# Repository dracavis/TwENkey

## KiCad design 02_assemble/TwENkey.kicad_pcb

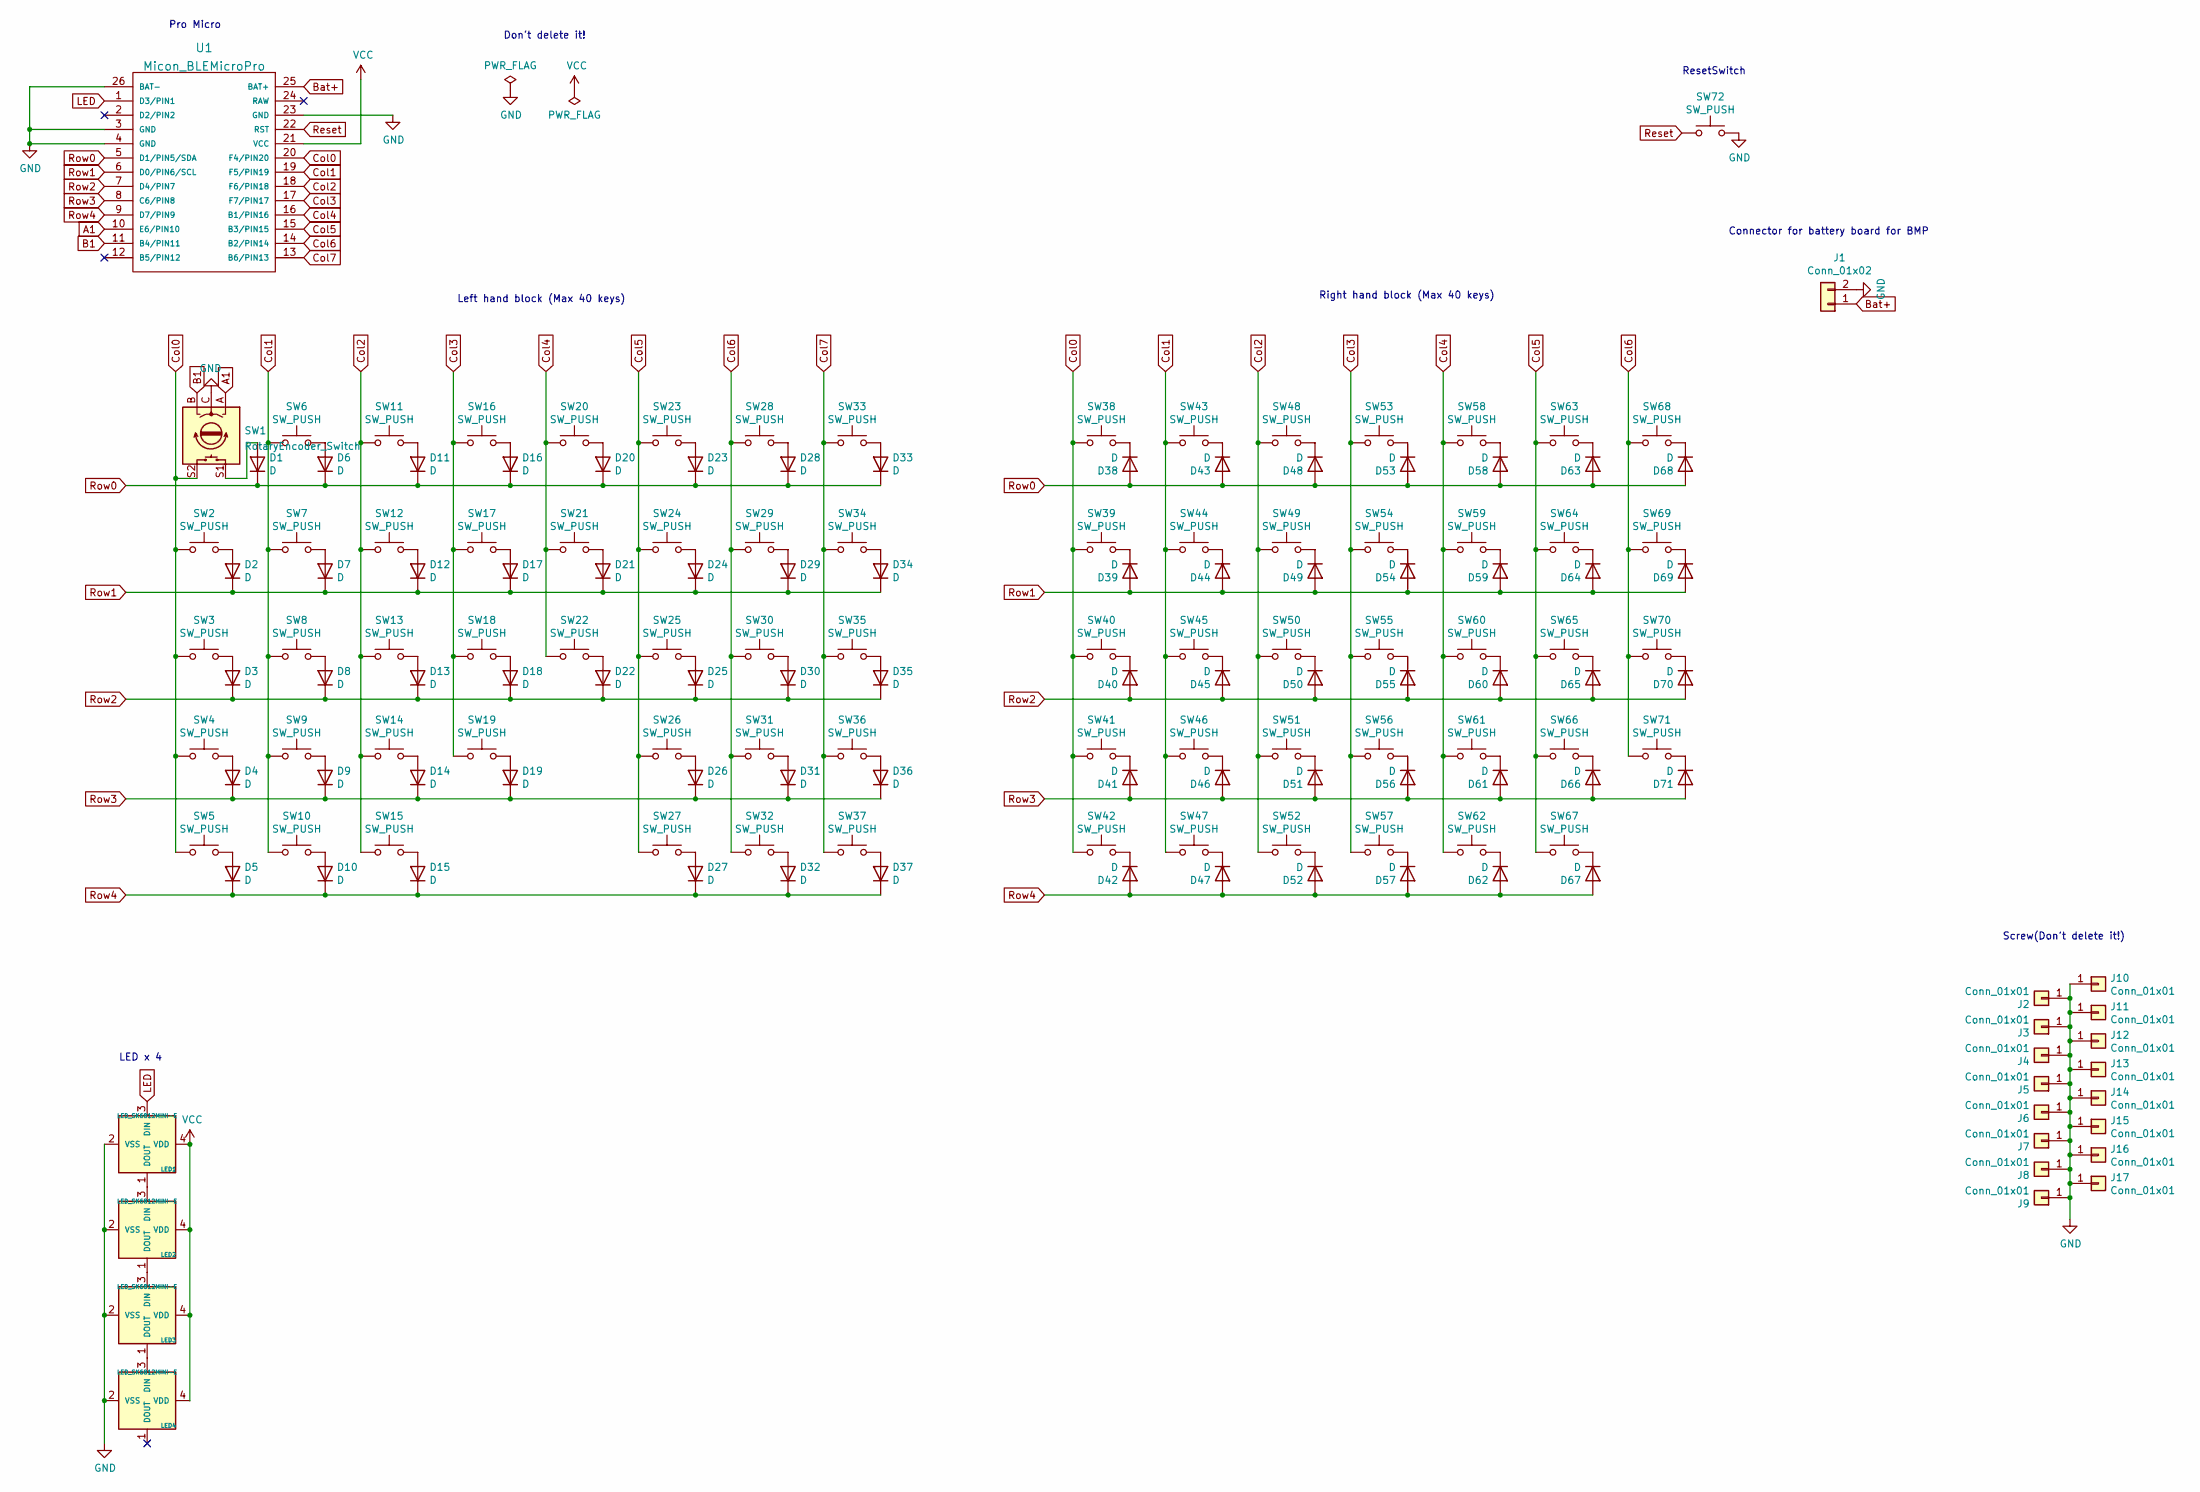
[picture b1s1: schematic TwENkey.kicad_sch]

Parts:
D1, D2, D3, D4, D5, D6, D7, D8, D9, D10, D11, D12, D13, D14, D15, D16, D17, D18, D19, D20, D21, D22, D23, D24, D25, D26, D27, D28, D29, D30, D31, D32, D33, D34, D35, D36, D37, D38, D39, D40, D41, D42, D43, D44, D45, D46, D47, D48, D49, D50, D51, D52, D53, D54, D55, D56, D57, D58, D59, D60, D61, D62, D63, D64, D65, D66, D67, D68, D69, D70, D71: D; Diode_TH_SMD
J1: Conn_01x02; Battery_XH2.5_GL_PCB
J2, J6, J7, J8, J9, J11, J13, J15, J16, J17: Conn_01x01; m2_Screw_Hole_Fab
J3, J4, J5, J10, J12, J14: Conn_01x01; m2_Screw_Hole_EdgeCuts
LED1, LED2, LED3, LED4: LED_SK6812MINI-E; LED_SK6812MINI-E_BL
SW1: RotaryEncoder_Switch; RotaryEncoder_EC12E
SW2, SW3, SW4, SW5, SW6, SW7, SW8, SW9, SW10, SW11, SW12, SW13, SW14, SW15, SW16, SW17, SW18, SW20, SW21, SW22, SW23, SW24, SW25, SW27, SW28, SW29, SW30, SW31, SW32, SW33, SW34, SW35, SW36, SW37, SW38, SW39, SW40, SW41, SW42, SW43, SW44, SW45, SW46, SW47, SW48, SW49, SW50, SW51, SW52, SW53, SW54, SW55, SW56, SW57, SW58, SW59, SW60, SW61, SW62, SW63, SW64, SW65, SW66, SW67, SW68, SW69, SW70: SW_PUSH; CherryMX_Hotswap_1u
SW19, SW26, SW71: SW_PUSH; CherryMX_Hotswap_2u
SW72: SW_PUSH; ResetSW
U1: Micon_BLEMicroPro; Micon_BLE

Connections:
A1: SW1.A, U1.10 (E6/PIN10)
B1: SW1.B, U1.11 (B4/PIN11)
Bat+: J1.1, U1.25 (BAT+)
Col0: SW1.S2, SW2.1, SW3.1, SW4.1, SW5.1, SW38.1, SW39.1, SW40.1, SW41.1, SW42.1, U1.20 (F4/PIN20)
Col1: SW6.1, SW7.1, SW8.1, SW9.1, SW10.1, SW43.1, SW44.1, SW45.1, SW46.1, SW47.1, U1.19 (F5/PIN19)
Col2: SW11.1, SW12.1, SW13.1, SW14.1, SW15.1, SW48.1, SW49.1, SW50.1, SW51.1, SW52.1, U1.18 (F6/PIN18)
Col3: SW16.1, SW17.1, SW18.1, SW19.1, SW53.1, SW54.1, SW55.1, SW56.1, SW57.1, U1.17 (F7/PIN17)
Col4: SW20.1, SW21.1, SW22.1, SW58.1, SW59.1, SW60.1, SW61.1, SW62.1, U1.16 (B1/PIN16)
Col5: SW23.1, SW24.1, SW25.1, SW26.1, SW27.1, SW63.1, SW64.1, SW65.1, SW66.1, SW67.1, U1.15 (B3/PIN15)
Col6: SW28.1, SW29.1, SW30.1, SW31.1, SW32.1, SW68.1, SW69.1, SW70.1, SW71.1, U1.14 (B2/PIN14)
Col7: SW33.1, SW34.1, SW35.1, SW36.1, SW37.1, U1.13 (B6/PIN13)
Data: J2.B, U1.2 (D2/PIN2)
GND: J1.2, J2.1, J2.C, J3.1, J4.1, J5.1, J6.1, J7.1, J8.1, J9.1, J10.1, J11.1, J12.1, J13.1, J14.1, J15.1, J16.1, J17.1, LED1.2 (VSS), LED2.2 (VSS), LED3.2 (VSS), LED4.2 (VSS), SW1.C, SW72.2, U1.3 (GND), U1.4 (GND), U1.23 (GND), U1.26 (BAT-)
LED: LED1.3 (DIN), U1.1 (D3/PIN1)
unnamed: D1.2 (A), SW1.S1
unnamed: D2.2 (A), SW2.2
unnamed: D3.2 (A), SW3.2
unnamed: D4.2 (A), SW4.2
unnamed: D5.2 (A), SW5.2
unnamed: D6.2 (A), SW6.2
unnamed: D7.2 (A), SW7.2
unnamed: D8.2 (A), SW8.2
unnamed: D9.2 (A), SW9.2
unnamed: D10.2 (A), SW10.2
unnamed: D11.2 (A), SW11.2
unnamed: D12.2 (A), SW12.2
unnamed: D13.2 (A), SW13.2
unnamed: D14.2 (A), SW14.2
unnamed: D15.2 (A), SW15.2
unnamed: D16.2 (A), SW16.2
unnamed: D17.2 (A), SW17.2
unnamed: D18.2 (A), SW18.2
unnamed: D19.2 (A), SW19.2
unnamed: D20.2 (A), SW20.2
unnamed: D21.2 (A), SW21.2
unnamed: D22.2 (A), SW22.2
unnamed: D23.2 (A), SW23.2
unnamed: D24.2 (A), SW24.2
unnamed: D25.2 (A), SW25.2
unnamed: D26.2 (A), SW26.2
unnamed: D27.2 (A), SW27.2
unnamed: D28.2 (A), SW28.2
unnamed: D29.2 (A), SW29.2
unnamed: D30.2 (A), SW30.2
unnamed: D31.2 (A), SW31.2
unnamed: D32.2 (A), SW32.2
unnamed: D33.2 (A), SW33.2
unnamed: D34.2 (A), SW34.2
unnamed: D35.2 (A), SW35.2
unnamed: D36.2 (A), SW36.2
unnamed: D37.2 (A), SW37.2
unnamed: D38.1 (K), SW38.2
unnamed: D39.1 (K), SW39.2
unnamed: D40.1 (K), SW40.2
unnamed: D41.1 (K), SW41.2
unnamed: D42.1 (K), SW42.2
unnamed: D43.1 (K), SW43.2
unnamed: D44.1 (K), SW44.2
unnamed: D45.1 (K), SW45.2
unnamed: D46.1 (K), SW46.2
unnamed: D47.1 (K), SW47.2
unnamed: D48.1 (K), SW48.2
unnamed: D49.1 (K), SW49.2
unnamed: D50.1 (K), SW50.2
unnamed: D51.1 (K), SW51.2
unnamed: D52.1 (K), SW52.2
unnamed: D53.1 (K), SW53.2
unnamed: D54.1 (K), SW54.2
unnamed: D55.1 (K), SW55.2
unnamed: D56.1 (K), SW56.2
unnamed: D57.1 (K), SW57.2
unnamed: D58.1 (K), SW58.2
unnamed: D59.1 (K), SW59.2
unnamed: D60.1 (K), SW60.2
unnamed: D61.1 (K), SW61.2
unnamed: D62.1 (K), SW62.2
unnamed: D63.1 (K), SW63.2
unnamed: D64.1 (K), SW64.2
unnamed: D65.1 (K), SW65.2
unnamed: D66.1 (K), SW66.2
unnamed: D67.1 (K), SW67.2
unnamed: D68.1 (K), SW68.2
unnamed: D69.1 (K), SW69.2
unnamed: D70.1 (K), SW70.2
unnamed: D71.1 (K), SW71.2
unnamed: LED1.1 (DOUT), LED2.3 (DIN)
unnamed: LED2.1 (DOUT), LED3.3 (DIN)
unnamed: LED3.1 (DOUT), LED4.3 (DIN)
Reset: SW72.1, U1.22 (RST)
Row0: D1.1 (K), D6.1 (K), D11.1 (K), D16.1 (K), D20.1 (K), D23.1 (K), D28.1 (K), D33.1 (K), D38.2 (A), D43.2 (A), D48.2 (A), D53.2 (A), D58.2 (A), D63.2 (A), D68.2 (A), U1.5 (D1/PIN5/SDA)
Row1: D2.1 (K), D7.1 (K), D12.1 (K), D17.1 (K), D21.1 (K), D24.1 (K), D29.1 (K), D34.1 (K), D39.2 (A), D44.2 (A), D49.2 (A), D54.2 (A), D59.2 (A), D64.2 (A), D69.2 (A), U1.6 (D0/PIN6/SCL)
Row2: D3.1 (K), D8.1 (K), D13.1 (K), D18.1 (K), D22.1 (K), D25.1 (K), D30.1 (K), D35.1 (K), D40.2 (A), D45.2 (A), D50.2 (A), D55.2 (A), D60.2 (A), D65.2 (A), D70.2 (A), U1.7 (D4/PIN7)
Row3: D4.1 (K), D9.1 (K), D14.1 (K), D19.1 (K), D26.1 (K), D31.1 (K), D36.1 (K), D41.2 (A), D46.2 (A), D51.2 (A), D56.2 (A), D61.2 (A), D66.2 (A), D71.2 (A), U1.8 (C6/PIN8)
Row4: D5.1 (K), D10.1 (K), D15.1 (K), D27.1 (K), D32.1 (K), D37.1 (K), D42.2 (A), D47.2 (A), D52.2 (A), D57.2 (A), D62.2 (A), D67.2 (A), U1.9 (D7/PIN9)
VCC: J2.D, LED1.4 (VDD), LED2.4 (VDD), LED3.4 (VDD), LED4.4 (VDD), U1.21 (VCC)

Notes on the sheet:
Connector for battery board for BMP
Pro Micro
Don't delete it!
Left hand block (Max 40 keys)
Screw(Don't delete it!)
ResetSwitch
LED x 4
Right hand block (Max 40 keys)

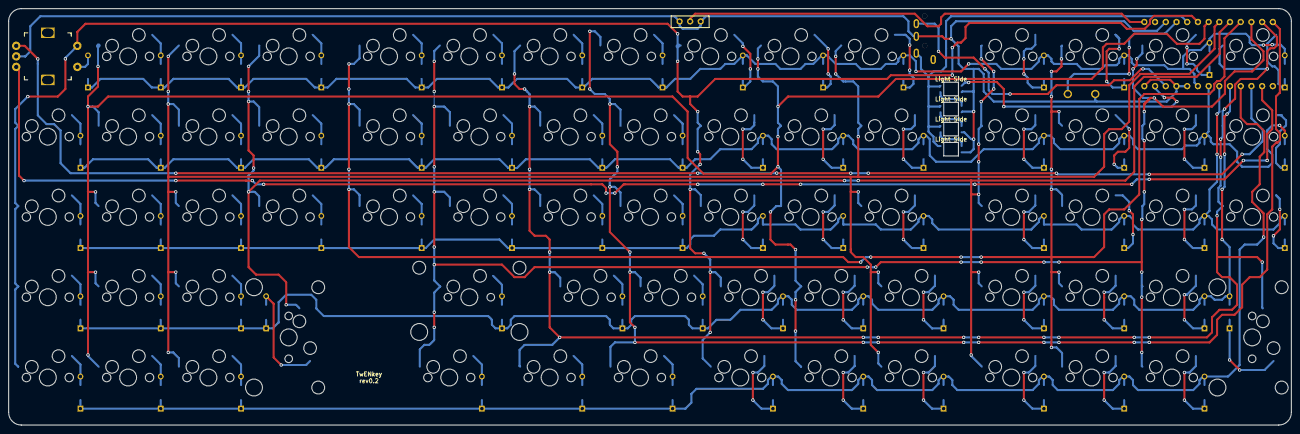
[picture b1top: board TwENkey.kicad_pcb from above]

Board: 2 copper layers, 304.4 x 98.8 mm, 150 parts (0 on the bottom side), 95 nets.

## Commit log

2022-01-01 upload
    upload
2022-01-02 サリチル酸さんのレビューを受けて修正
2022-01-02 TRRSコネクタを追加
